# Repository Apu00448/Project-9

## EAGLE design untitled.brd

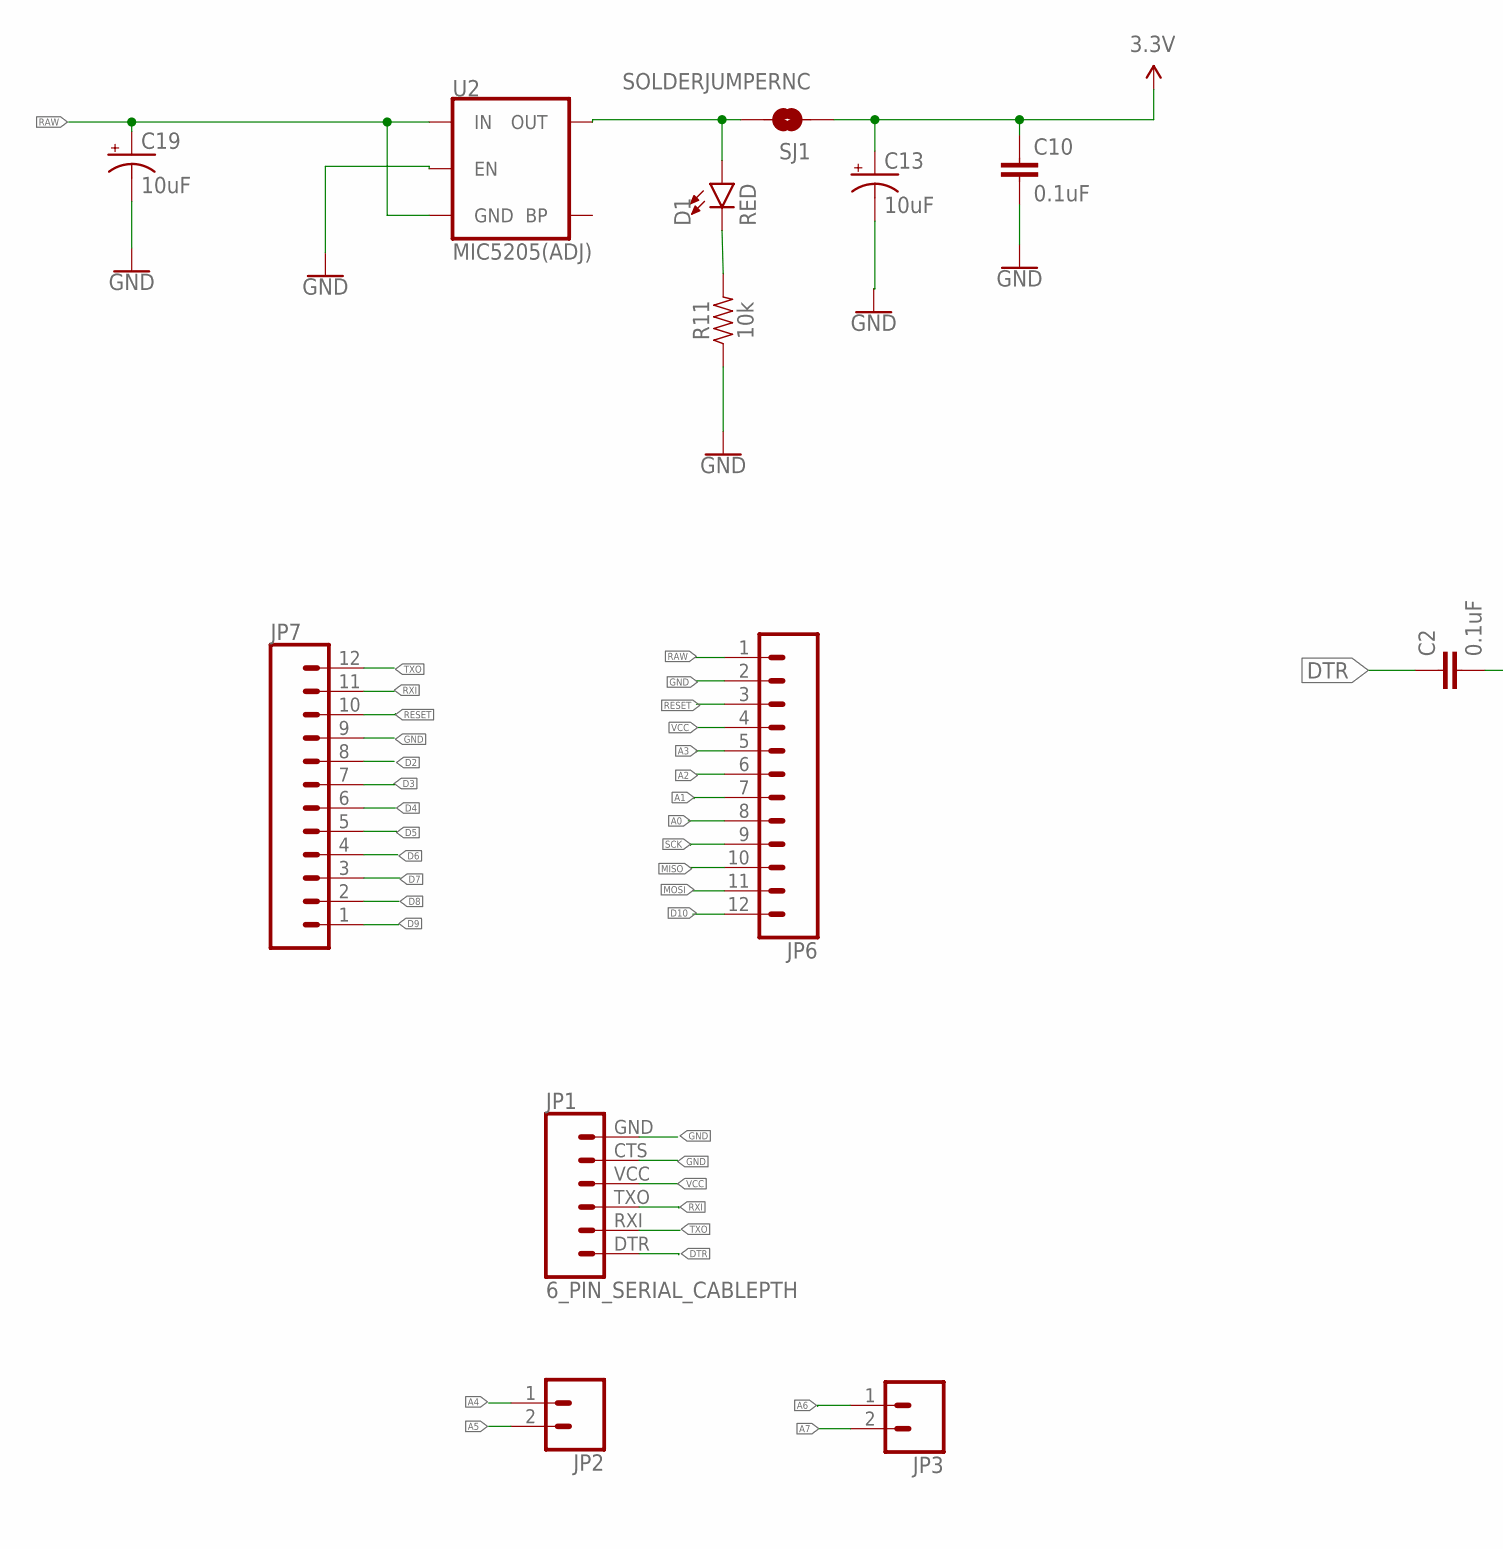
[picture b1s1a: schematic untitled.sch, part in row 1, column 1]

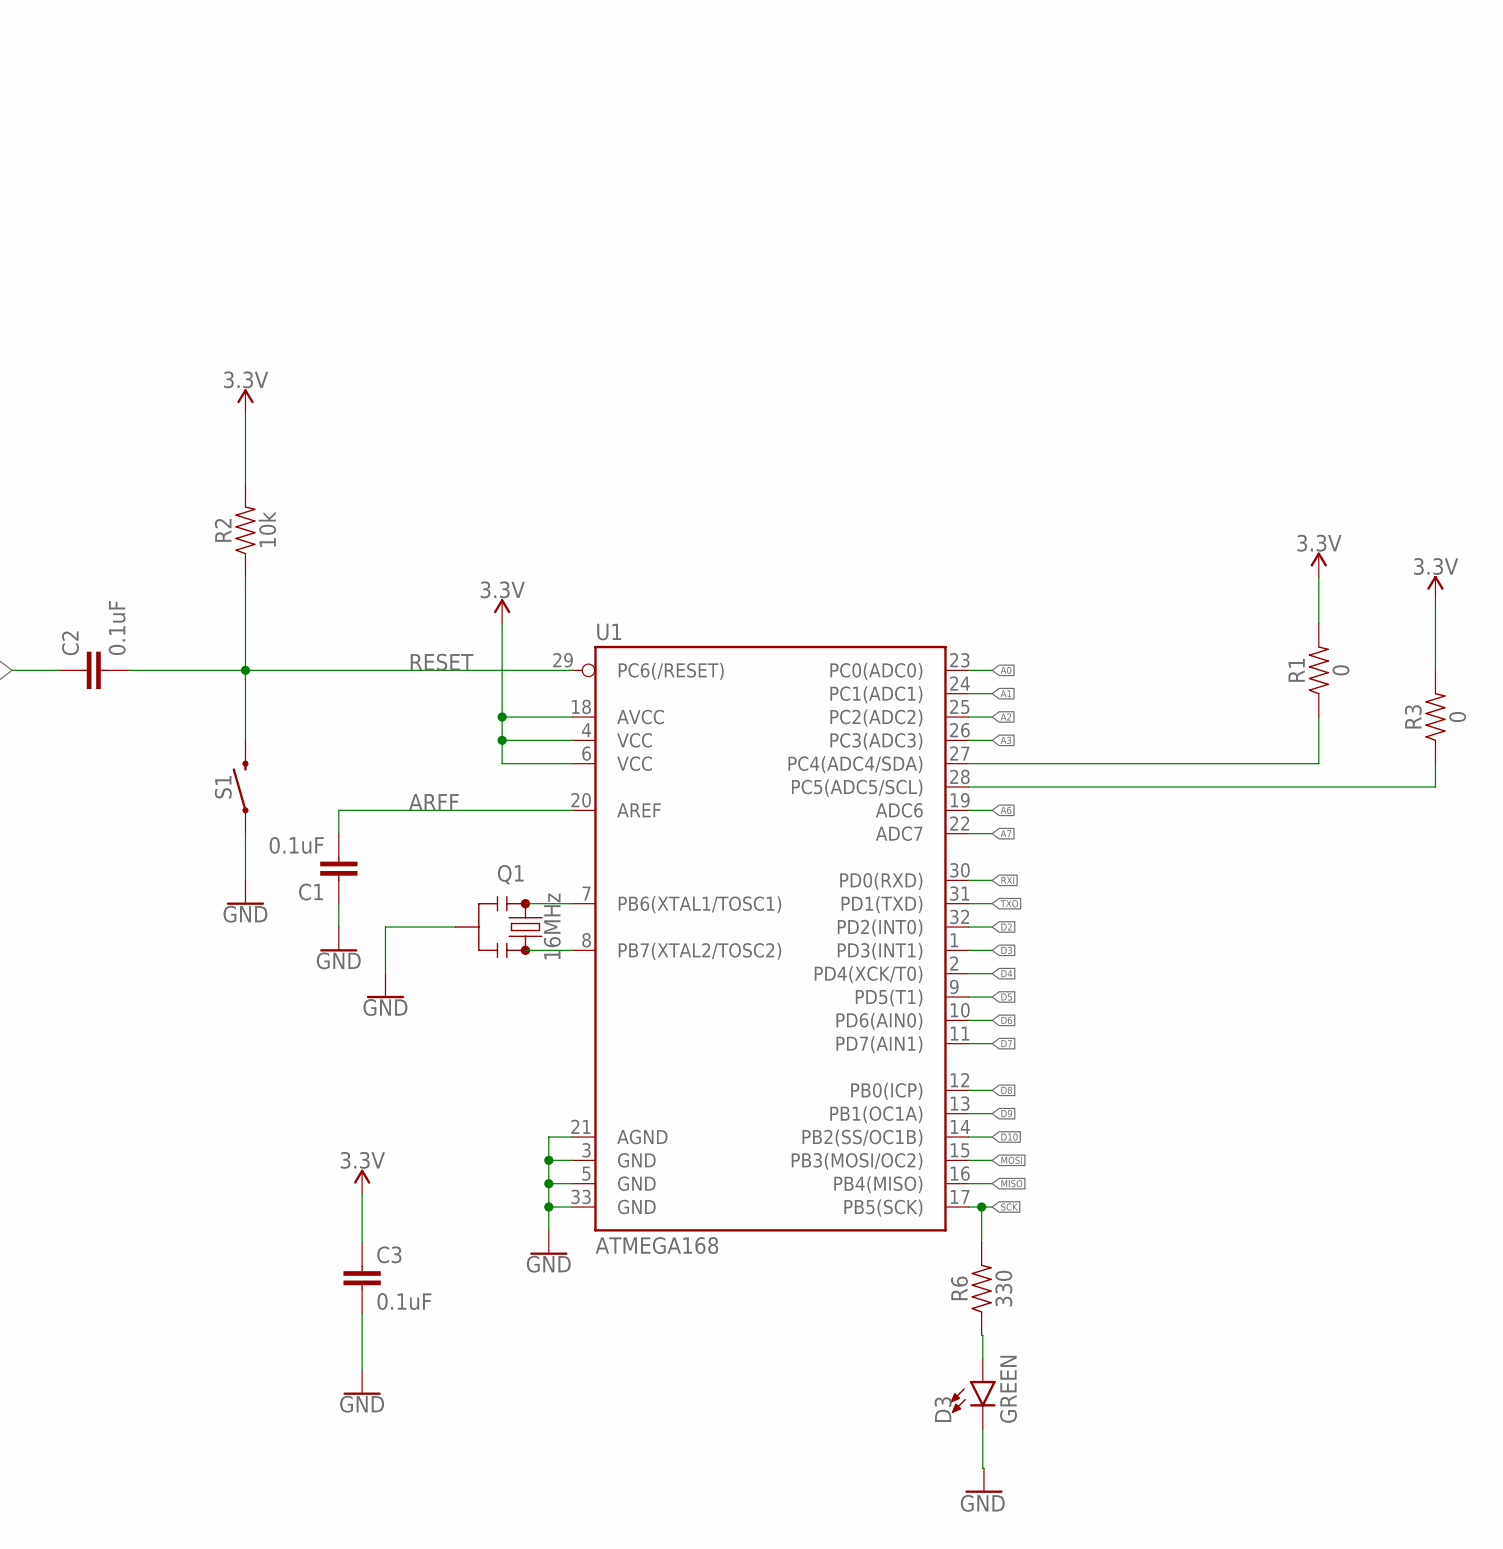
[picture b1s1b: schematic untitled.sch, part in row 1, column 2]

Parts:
C1, C2, C3, C10: 0.1uF; 0603
C13, C19: 10uF; 0603-POLAR
D1: RED; LED-0603
D3: GREEN; LED-0603
JP1: 6_PIN_SERIAL_CABLEPTH; FTDI_BASIC
JP2, JP3: CONN_02; 1X02
JP6, JP7: CONN_12; 1X12
Q1: 16MHz; RESONATOR-SMD-3.2X1.3
R1, R3: 0; 0603
R2, R11: 10k; 0603
R6: 330; 0603
S1: MOMENTARY-SWITCH-SPST-SMD-5.2-TALL-REDUNDANT; TACTILE_SWITCH_SMD_5.2MM
SJ1: SOLDERJUMPERNC; SJ_2S
U1: ATMEGA168; MLF32
U2: MIC5205(ADJ); SOT23-5

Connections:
3.3V: C3.1, C10.1, C13.+, R1.2, R2.2, R3.2, SJ1.1, U1.4 (VCC), U1.6 (VCC), U1.18 (AVCC)
A0: JP6.8, U1.23 (PC0(ADC0))
A1: JP6.7, U1.24 (PC1(ADC1))
A2: JP6.6, U1.25 (PC2(ADC2))
A3: JP6.5, U1.26 (PC3(ADC3))
A4: JP2.1
A5: JP2.2
A6: JP3.1, U1.19 (ADC6)
A7: JP3.2, U1.22 (ADC7)
ARFF: C1.2, U1.20 (AREF)
D2: JP7.8, U1.32 (PD2(INT0))
D3: JP7.7, U1.1 (PD3(INT1))
D4: JP7.6, U1.2 (PD4(XCK/T0))
D5: JP7.5, U1.9 (PD5(T1))
D6: JP7.4, U1.10 (PD6(AIN0))
D7: JP7.3, U1.11 (PD7(AIN1))
D8: JP7.2, U1.12 (PB0(ICP))
D9: JP7.1, U1.13 (PB1(OC1A))
D10: JP6.12, U1.14 (PB2(SS/OC1B))
DTR: C2.1, JP1.DTR (1)
GND: C1.1, C3.2, C10.2, C13.-, C19.-, D3.C, JP1.CTS (5), JP1.GND (6), JP6.2, JP7.9, Q1.2, R11.1, S1.1, S1.2 (1), U1.3 (GND), U1.5 (GND), U1.21 (AGND), U1.33 (GND), U2.3 (EN)
MISO: JP6.10, U1.16 (PB4(MISO))
MOSI: JP6.11, U1.15 (PB3(MOSI/OC2))
unnamed: Q1.3, U1.8 (PB7(XTAL2/TOSC2))
unnamed: Q1.1, U1.7 (PB6(XTAL1/TOSC1))
unnamed: R1.1, U1.27 (PC4(ADC4/SDA))
unnamed: R3.1, U1.28 (PC5(ADC5/SCL))
unnamed: D3.A, R6.1
unnamed: D1.A, SJ1.2, U2.5 (OUT)
unnamed: D1.C, R11.2
RAW: C19.+, JP6.1, U2.1 (IN), U2.2 (GND)
RESET: C2.2, JP6.3, JP7.10, R2.1, S1.3 (2), S1.4 (2), U1.29 (PC6(/RESET))
RXI: JP1.TXO (3), JP7.11, U1.30 (PD0(RXD))
SCK: JP6.9, R6.2, U1.17 (PB5(SCK))
TXO: JP1.RXI (2), JP7.12, U1.31 (PD1(TXD))
VCC: JP1.VCC (4), JP6.4

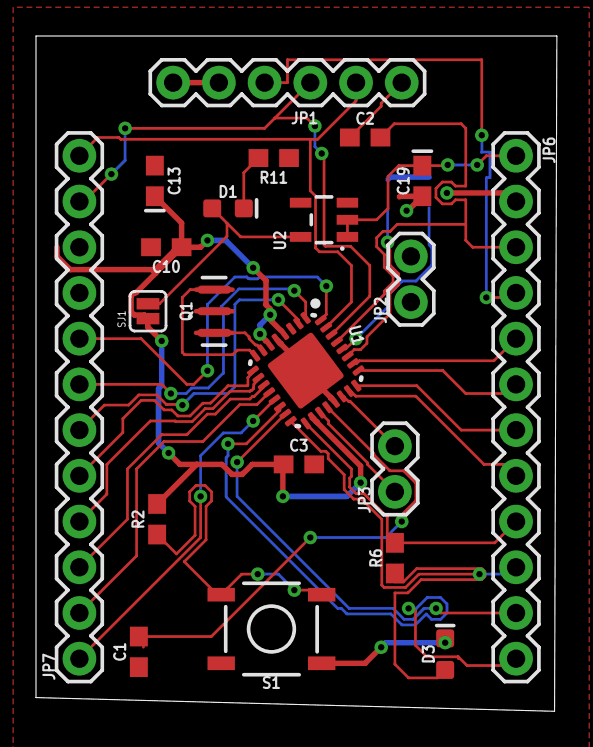
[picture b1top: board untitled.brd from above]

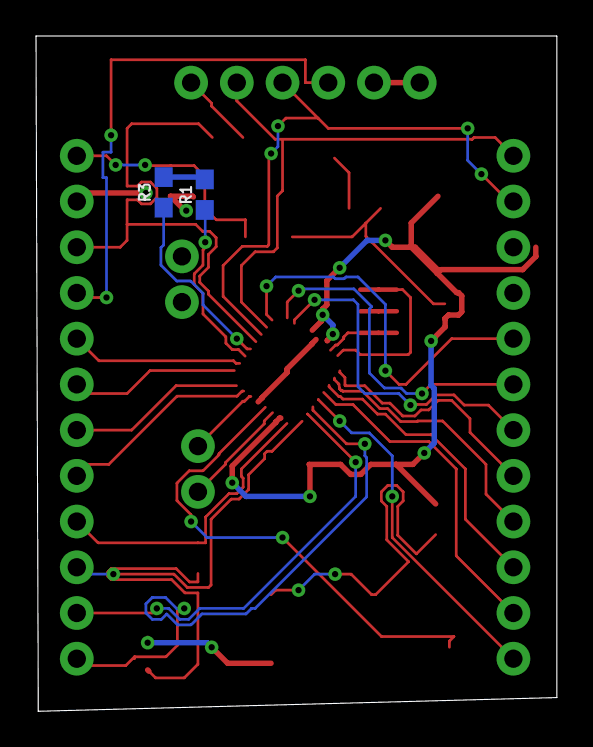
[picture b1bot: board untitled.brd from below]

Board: 2 copper layers, 28.9 x 37.5 mm, 23 parts (2 on the bottom side), 34 nets.

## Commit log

2024-01-03 Arduino Pro Mini-- Eagle

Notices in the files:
parts and their libraries:
SparkFun-IC-Microcontroller: Licensing: Creative Commons ShareAlike 4.0 International - https://creativecommons.org/licenses/by-sa/4.0
